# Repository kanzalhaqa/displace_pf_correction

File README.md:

<br>
<p align="center">
    <h1 align="center">⭐&emsp;KANZAL HAQ A&emsp;⭐</h1>
</p>

<br>
<!--  -->
<p align="center">

</p>

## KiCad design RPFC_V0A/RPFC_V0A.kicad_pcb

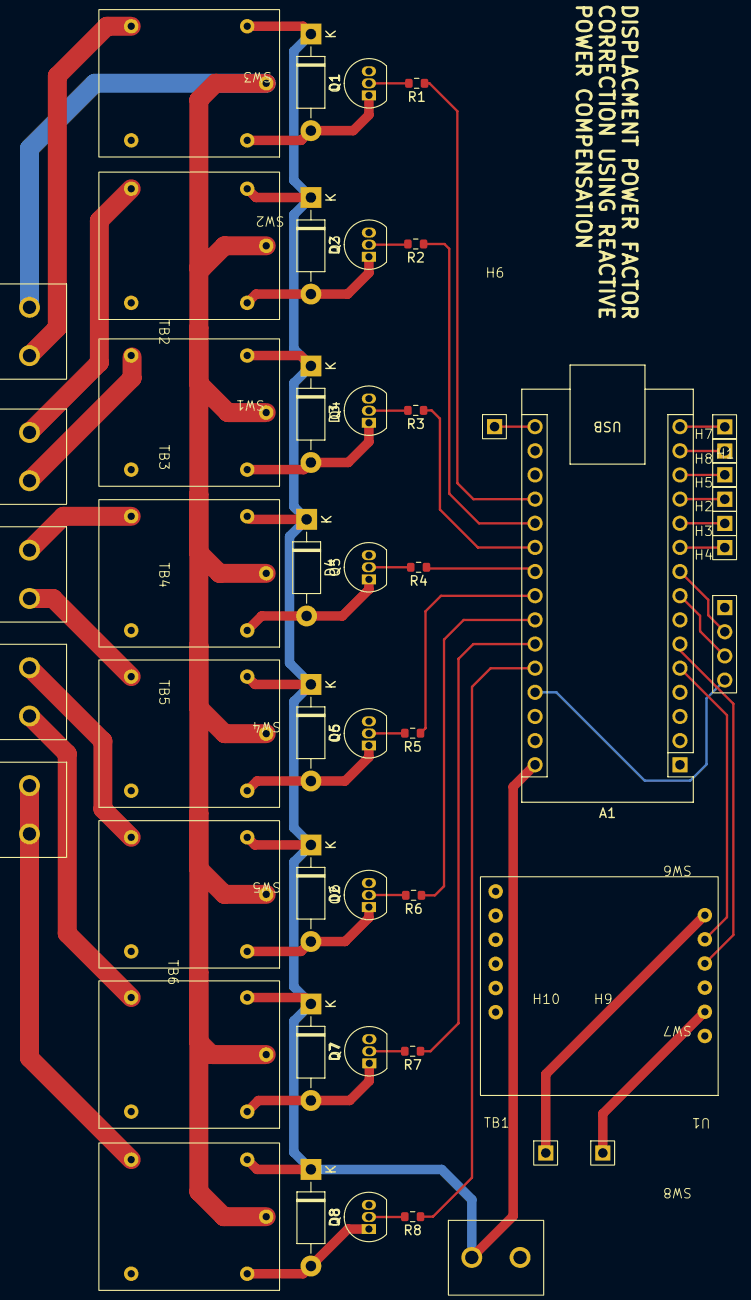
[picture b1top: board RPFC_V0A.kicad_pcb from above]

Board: 2 copper layers, 50 parts (0 on the bottom side), 49 nets.

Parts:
A1: Arduino_Nano_Every; Arduino_Nano
D1, D2, D3, D4, D5, D6, D7, D8: 1N4007; D_DO-41_SOD81_P10.16mm_Horizontal
H1: 4pin_header
H2, H3, H4, H5, H6, H7, H8, H9, H10: 1pin_header
Q1, Q2, Q3, Q4, Q5, Q6, Q7, Q8: BC547; TO-92_Inline
R1, R2, R3, R4, R5, R6, R7, R8: R0603_1k; R_0603_1608Metric
SW1, SW2, SW3, SW4, SW5, SW6, SW7, SW8: JQC-3FC(T73) DC5V
TB1, TB2, TB3, TB4, TB5, TB6: Terminal_block_2pos; TB_2pin
U1: SIM800L; GSM M1

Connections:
+5V: A1.27 (+5V), H1.4
/PZEMRX: A1.8 (D5), H1.3
/PZEMTX: A1.9 (D6), H1.2
/switching_circuit/A0: A1.19 (A0), R1.1
/switching_circuit/A1: A1.20 (A1), R2.1
/switching_circuit/A2: A1.21 (A2), R3.1
/switching_circuit/A3: A1.22 (A3), R4.1
/switching_circuit/A4: A1.23 (SDA/A4), R5.1
/switching_circuit/A5: A1.24 (SCL/A5), R6.1
/switching_circuit/A6: A1.25 (A6), R7.1
/switching_circuit/A7: A1.26 (A7), R8.1
/switching_circuit/COM: SW1.1 (COM), SW2.1 (COM), SW3.1 (COM), SW4.1 (COM), SW5.1 (COM), SW6.1 (COM), SW7.1 (COM), SW8.1 (COM), TB2.1 (+ve)
/switching_circuit/SW_C1: SW1.5 (NO), TB2.2 (-ve)
/switching_circuit/SW_C2: SW2.5 (NO), TB3.1 (+ve)
/switching_circuit/SW_C3: SW3.5 (NO), TB3.2 (-ve)
/switching_circuit/SW_C4: SW4.5 (NO), TB4.1 (+ve)
/switching_circuit/SW_C5: SW5.5 (NO), TB4.2 (-ve)
/switching_circuit/SW_C6: SW6.5 (NO), TB5.1 (+ve)
/switching_circuit/SW_C7: SW7.5 (NO), TB5.2 (-ve)
/switching_circuit/SW_C8: SW8.5 (NO), TB6.1 (+ve), TB6.2 (-ve)
D7: A1.10 (D7), H4.1
D8: A1.11 (D8), H3.1
D9: A1.12 (D9), H2.1
D10: A1.13 (D10), H5.1
GND: A1.4 (GND), A1.29 (GND), H1.1, Q1.3 (E), Q2.3 (E), Q3.3 (E), Q4.3 (E), Q5.3 (E), Q6.3 (E), Q7.3 (E), Q8.3 (E), TB1.2 (-ve)
GND_buck: H10.1, U1.12 (GND)
MISO: A1.15 (MISO), H7.1
MOSI: A1.14 (MOSI), H8.1
unnamed: D1.2 (A), Q1.1 (C), SW1.3 (-ve)
unnamed: D2.2 (A), Q3.1 (C), SW2.3 (-ve)
unnamed: D3.2 (A), Q4.1 (C), SW3.3 (-ve)
unnamed: D4.2 (A), Q5.1 (C), SW4.3 (-ve)
unnamed: D5.2 (A), Q6.1 (C), SW5.3 (-ve)
unnamed: D6.2 (A), Q2.1 (C), SW6.3 (-ve)
unnamed: D7.2 (A), Q7.1 (C), SW7.3 (-ve)
unnamed: D8.2 (A), Q8.1 (C), SW8.3 (-ve)
unnamed: Q1.2 (B), R1.2
unnamed: Q2.2 (B), R6.2
unnamed: Q3.2 (B), R2.2
unnamed: Q4.2 (B), R3.2
unnamed: Q5.2 (B), R4.2
unnamed: Q6.2 (B), R5.2
unnamed: Q7.2 (B), R7.2
unnamed: Q8.2 (B), R8.2
SCK: A1.16 (SCK), H6.1
SIMTX: A1.5 (D2), U1.11 (TXD)
VIN: A1.30 (VIN), D1.1 (K), D2.1 (K), D3.1 (K), D4.1 (K), D5.1 (K), D6.1 (K), D7.1 (K), D8.1 (K), SW1.2 (+ve), SW2.2 (+ve), SW3.2 (+ve), SW4.2 (+ve), SW5.2 (+ve), SW6.2 (+ve), SW7.2 (+ve), SW8.2 (+ve), TB1.1 (+ve)
VIN_buck: H9.1, U1.8 (VCC)
~SIMRX: A1.6 (D3), U1.10 (RXD)
